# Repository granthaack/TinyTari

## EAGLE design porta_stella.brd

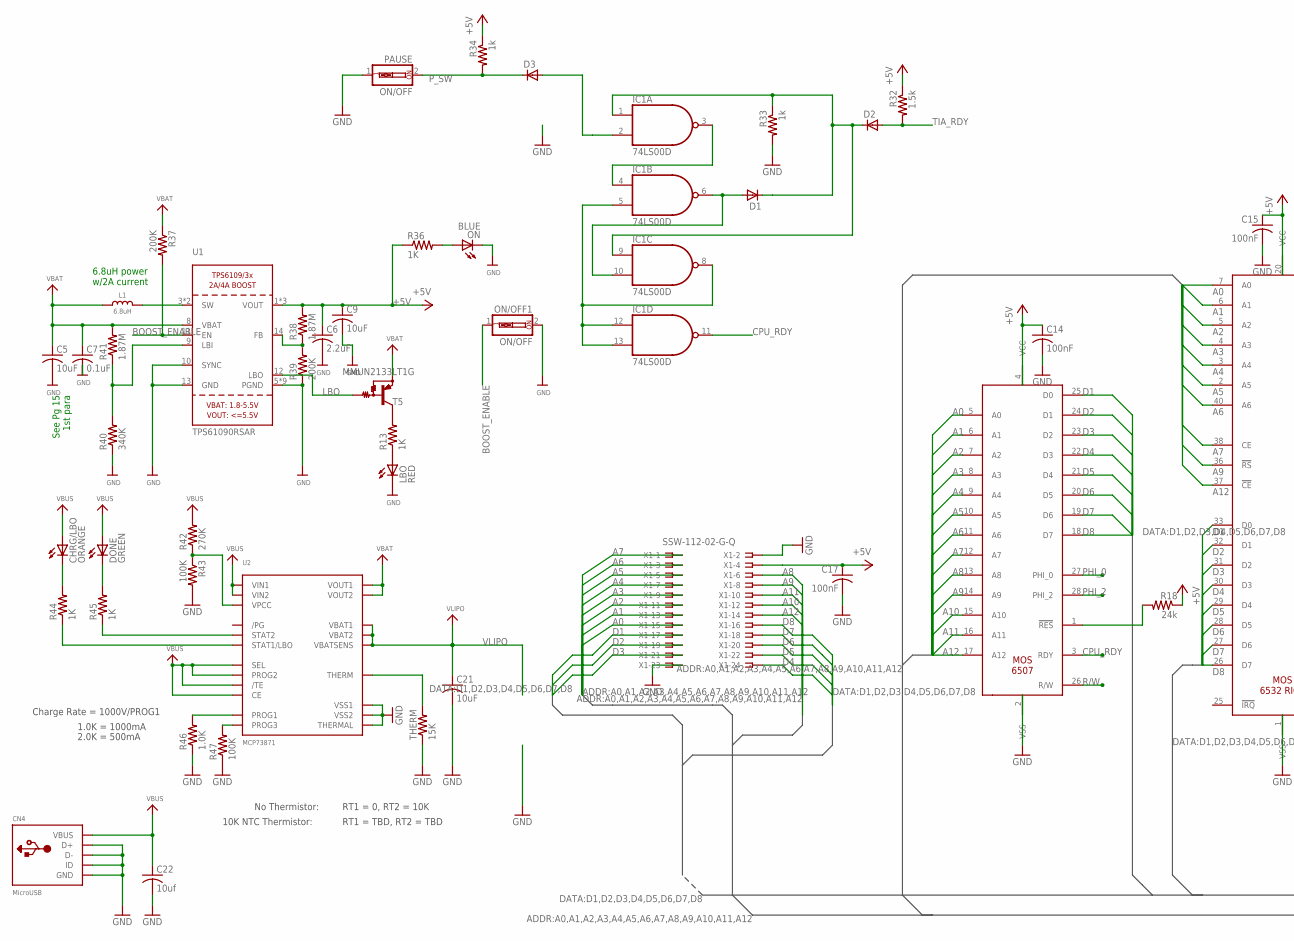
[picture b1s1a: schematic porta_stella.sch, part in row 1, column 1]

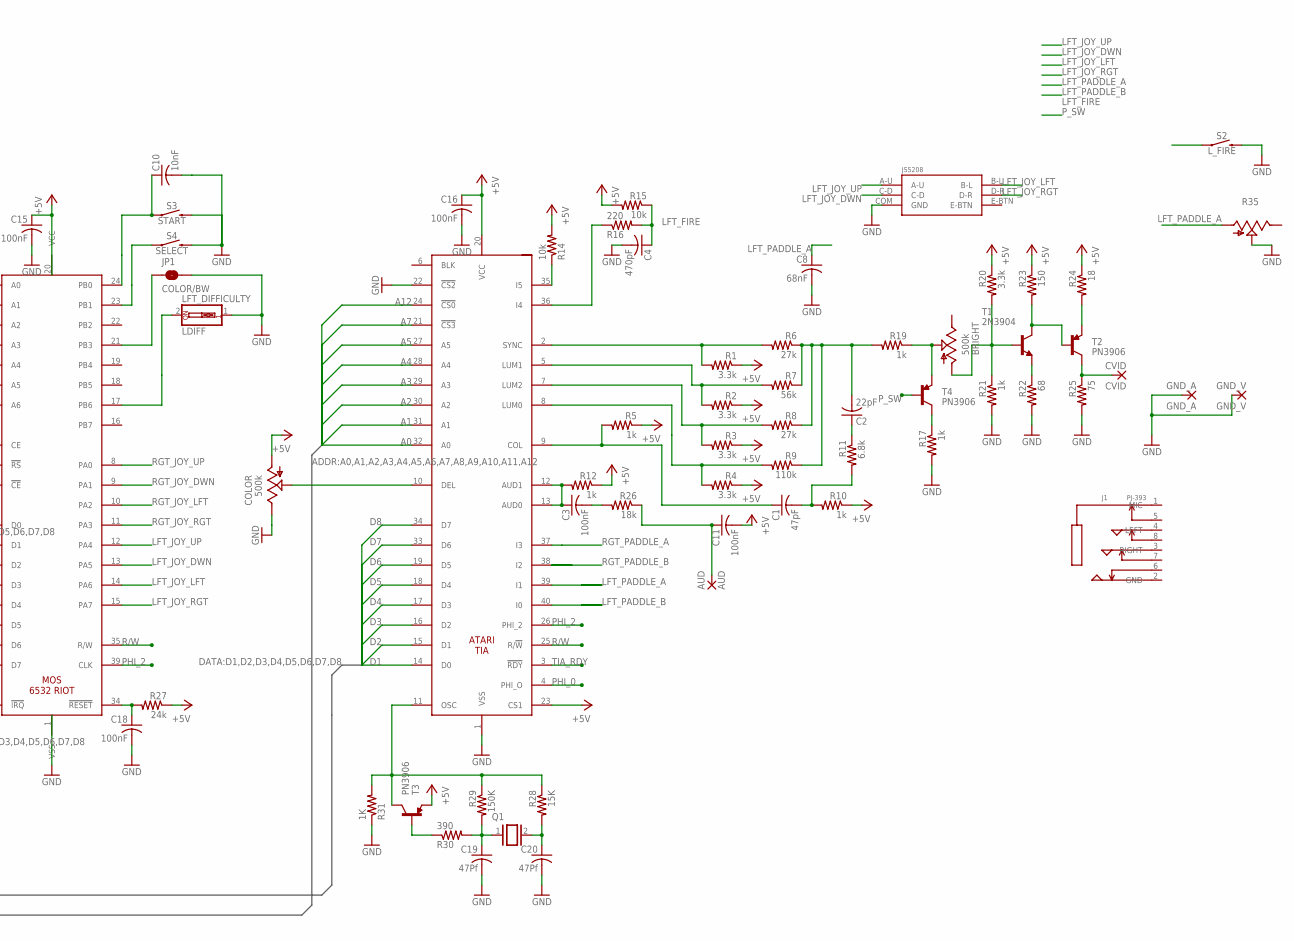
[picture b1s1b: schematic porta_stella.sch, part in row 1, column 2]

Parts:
6507: MOS_6507; DIL28
6532: MOS_6532; DIL40
AUD: AUD; 2,54/1,1
BRIGHT: 500k; 3223G
C1: 47pF; C0805
C2: 22pF; C0805
C3, C11, C14, C15, C16, C17, C18: 100nF; C0805
C4: 470pF; C0805
C5, C9, C21: 10uF; C1210
C6: 2.2uF; C0805
C7: 0.1uF; C0805
C8: 68nF; C0805
C10: 10nF; C0805
C19, C20: 47Pf; C0805
C22: 10uf; C0805
CHRG/LBO: ORANGE; ADAFRUIT_CHIPLED_0603
CN4: MicroUSB; 4UCONN_20329
COLOR: 500k; 3223G
CVID: CVID; 2,54/1,1
D1, D2, D3: DIODE_E-; DIODE_SMB
DONE: GREEN; ADAFRUIT_CHIPLED_0603
GND_A: GND_A; 2,54/1,1
GND_V: GND_V; 2,54/1,1
IC1: 74LS00D; SO14
J1: PJ-393; AUDIO8P-SMD-3.5-14.5X6.1X4.0MM
JP1: COLOR/BW; SMT-JUMPER_2_NO_NO-SILK
L1: 6.8uH; INDUCTOR_5X5MM_TDK_VLC5045
LBO: RED; ADAFRUIT_CHIPLED_0603
LDIFF: LFT_DIFFICULTY; EDG-01
ON: BLUE; ADAFRUIT_CHIPLED_0603
ON/OFF1: ON/OFF; EDG-01
PAUSE: ON/OFF; EDG-01
Q1: XTAL/S; QS
R1, R2, R3, R4, R20: 3.3k; M0805
R5, R10, R12, R17, R19, R21, R33, R34: 1k; M0805
R6, R8: 27k; M0805
R7: 56k; M0805
R9: 110k; M0805
R11: 6.8k; M0805
R13, R36, R44, R45: 1K; R0805
R14, R15: 10k; M0805
R16: 220; M0805
R18, R27: 24k; M0805
R22: 68; M0805
R23: 150; M0805
R24: 18; M0805
R25: 75; M0805
R26: 18k; M0805
R28: 15K; M0805
R29: 150K; M0805
R30: 390; M0805
R31: 1K; M0805
R32: 1.5k; M0805
R35: TRIM_US-ECP10S; ECP10S
R37, R39: 200K; R0805
R38, R41: 1.87M; R0805
R40: 340K; R0805
R42: 270K; R0805
R43, R47: 100K; R0805
R46: 1.0K; R0805
S2: L_FIRE; TACTILE_SWITCH_SMD_5.2MM
S3: START; TACTILE_SWITCH_SMD_6.0X3.5MM
S4: SELECT; TACTILE_SWITCH_SMD_6.0X3.5MM
T1: 2N3904; SOT23-BEC
T2, T3, T4: PN3906; SOT23-3
T5: MMUN2133LT1G; TRANSISTOR_SC59-BEC
THERM: 15K; R0805
TIA: ATARI_TIA; DIL40
U1: TPS61090RSAR; PVQFN-16
U2: MCP73871; QFN20_4MM
U$5: JS5208; JS5208_PKG
X1: SSW-112-02-G-Q

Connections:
+5V: 6507.4 (VCC), 6532.20 (VCC), C6.1, C9.1, C11.2, C14.1, C15.1, C16.1, C17.1, COLOR.1 (A), R1.1, R2.1, R3.1, R4.1, R5.1, R10.1, R12.1, R14.2, R15.2, R18.1, R20.1, R23.1, R24.1, R27.1, R32.1, R34.1, R36.1, R38.2, T3.2 (E), TIA.20 (VCC), TIA.23 (CS1), U1.1 (VOUT), U1.15 (VOUT), U1.16 (VOUT), X1.4
A0: 6507.5 (A0), 6532.7 (A0), TIA.32 (A0), X1.15
A1: 6507.6 (A1), 6532.6 (A1), TIA.31 (A1), X1.13
A2: 6507.7 (A2), 6532.5 (A2), TIA.30 (A2), X1.11
A3: 6507.8 (A3), 6532.4 (A3), TIA.29 (A3), X1.9
A4: 6507.9 (A4), 6532.3 (A4), TIA.28 (A4), X1.7
A5: 6507.10 (A5), 6532.2 (A5), TIA.27 (A5), X1.5
A6: 6507.11 (A6), 6532.40 (A6), X1.3
A7: 6507.12 (A7), 6532.38 (CE), TIA.21 (!CS3), X1.1
A8: 6507.13 (A8), X1.6
A9: 6507.14 (A9), 6532.36 (!RS), X1.8
A10: 6507.15 (A10), X1.12
A11: 6507.16 (A11), X1.10
A12: 6507.17 (A12), 6532.37 (!CE), TIA.24 (!CS0), X1.14
BOOST_ENABLE: ON/OFF1.1, R37.2, U1.11 (EN); also elsewhere on the board
CPU_RDY: 6507.3 (RDY), IC1.11 (O)
CVID: CVID.1, R25.1, T2.3 (C); also elsewhere on the board
D1: 6507.25 (D0), 6532.33 (D0), TIA.14 (D0), X1.17
D2: 6507.24 (D1), 6532.32 (D1), TIA.15 (D1), X1.19
D3: 6507.23 (D2), 6532.31 (D2), TIA.16 (D2), X1.21
D4: 6507.22 (D3), 6532.30 (D3), TIA.17 (D3), X1.24
D5: 6507.21 (D4), 6532.29 (D4), TIA.18 (D4), X1.22
D6: 6507.20 (D5), 6532.28 (D5), TIA.19 (D5), X1.20
D7: 6507.19 (D6), 6532.27 (D6), TIA.33 (D6), X1.18
D8: 6507.18 (D7), 6532.26 (D7), TIA.34 (D7), X1.16
GND: 6507.2 (VSS), 6532.1 (VSS), C4.2, C5.2, C6.2, C7.2, C8.2, C9.2, C10.2, C14.2, C15.2, C16.2, C17.2, C18.2, C19.2, C20.2, C21.2, C22.2, CN4.BASE@1 (GND), CN4.BASE@2 (GND), CN4.D+, CN4.D-, CN4.GND, CN4.ID, CN4.SPRT@1 (GND), CN4.SPRT@2 (GND), CN4.SPRT@3 (GND), CN4.SPRT@4 (GND), COLOR.3 (E), GND_A.1, GND_V.1, IC1.7 (GND), J1.-, JP1.2, LBO.C, LDIFF.1, ON.C, ON/OFF1.2, PAUSE.1, PAUSE.P$1, PAUSE.P$2, PAUSE.P$4, PAUSE.P$5, R17.2, R21.2, R22.2, R25.2, R31.1, R33.2, R35.S, R39.1, R40.1, R43.2, R46.1, R47.1, S2.3 (2), S3.2, S4.2, THERM.1, TIA.1 (VSS), TIA.22 (!CS2), U1.5 (PGND), U1.6 (PGND), U1.7 (PGND), U1.10 (SYNC), U1.13 (GND), U1.P$18 (PGND), U1.P$19 (PGND), U1.P$20 (PGND), U1.P$21 (PGND), U1.P$22 (PGND), U1.THERMAL (PGND), U2.P$10 (VSS1), U2.P$11 (VSS2), U2.P$21 (THERMAL), U$5.COM (GND), X1.2, X1.23; also elsewhere on the board
LBO: T5.B, U1.12 (LBO)
LFT_FIRE: C4.1, R15.1, R16.2, S2.1; also elsewhere on the board
LFT_JOY_DWN: 6532.13 (PA5), U$5.C-D; also elsewhere on the board
LFT_JOY_LFT: 6532.14 (PA6), U$5.B-L; also elsewhere on the board
LFT_JOY_RGT: 6532.15 (PA7), U$5.D-R; also elsewhere on the board
LFT_JOY_UP: 6532.12 (PA4), U$5.A-U; also elsewhere on the board
LFT_PADDLE_A: C8.1, R35.A, TIA.39 (I1); also elsewhere on the board
LFT_PADDLE_B: TIA.40 (I0)
unnamed: R1.2, R6.2, TIA.2 (SYNC)
unnamed: R2.2, R7.2, TIA.5 (LUM1)
unnamed: R3.2, R8.2, TIA.7 (LUM2)
unnamed: R4.2, R9.2, TIA.8 (LUM0)
unnamed: C1.1, R5.2, TIA.9 (COL)
unnamed: C1.2, R10.2, R11.2
unnamed: C2.1, R11.1
unnamed: R14.1, TIA.35 (I5)
unnamed: L1.P$2 (2), U1.3 (SW), U1.4 (SW)
unnamed: R16.1, TIA.36 (I4)
unnamed: R40.2, R41.1, U1.9 (LBI)
unnamed 46: BRIGHT.2 (S), R19.1, T4.2 (E); also elsewhere on the board
unnamed 47: BRIGHT.1 (A), R20.2, R21.1, T1.B; also elsewhere on the board
unnamed: R22.1, T1.E
unnamed: R23.2, T1.C, T2.1 (B)
unnamed: COLOR.2 (S), TIA.10 (DEL)
unnamed: 6532.24 (PB0), C10.1, S3.1
unnamed: 6532.23 (PB1), S4.1
unnamed: 6532.21 (PB3), JP1.1
unnamed 54: 6532.17 (PB6), LDIFF.2; also elsewhere on the board
unnamed: LBO.A, R13.1
unnamed: 6507.1 (!RES), R18.2
unnamed: R24.2, T2.2 (E)
unnamed: C3.2, R26.2
unnamed: C3.1, R12.2, TIA.12 (AUD1), TIA.13 (AUD0)
unnamed: 6532.34 (!RESET), C18.1, R27.2
unnamed: C20.1, Q1.2, R28.2
unnamed: C19.1, Q1.1, R29.2, R30.2
unnamed: R28.1, R29.1, R31.2, T3.3 (C), TIA.11 (OSC)
unnamed: R30.1, T3.1 (B)
unnamed: R17.1, T4.3 (C)
unnamed: IC1.5 (I1), IC1.8 (O), IC1.12 (I0), IC1.13 (I1)
unnamed: D3.A (C), IC1.2 (I1)
unnamed: R38.1, R39.2, U1.14 (FB)
unnamed: IC1.3 (O), IC1.4 (I0)
unnamed: D1.A (C), IC1.6 (O), IC1.10 (I1)
unnamed: D1.C (A), D2.C (A), IC1.1 (I0), IC1.9 (I0), R33.1
unnamed: R13.2, T5.C
unnamed: ON.A, R36.2
unnamed: R42.1, R43.1, U2.P$2 (VPCC)
unnamed: R45.1, U2.P$7 (STAT2)
unnamed: R44.1, U2.P$8 (STAT1/LBO)
unnamed: R46.2, U2.P$13 (PROG1)
unnamed: THERM.2, U2.P$5 (THERM)
unnamed: DONE.C, R45.2
unnamed: CHRG/LBO.C, R44.2
unnamed: R47.2, U2.P$12 (PROG3)
PHI_0: 6507.27 (PHI_0), TIA.4 (PHI_O)
PHI_2: 6507.28 (PHI_2), 6532.39 (CLK), TIA.26 (PHI_2)
P_SW: D3.C (A), PAUSE.2, PAUSE.P$3, PAUSE.P$6, R34.2, T4.1 (B)
R/W: 6507.26 (R/W), 6532.35 (R/W), TIA.25 (R/!W)
RAW_CVID: C2.2, R6.1, R7.1, R8.1, R9.1, R19.2
RGT_JOY_DWN: 6532.9 (PA1)
RGT_JOY_LFT: 6532.10 (PA2)
RGT_JOY_RGT: 6532.11 (PA3)
RGT_JOY_UP: 6532.8 (PA0)
RGT_PADDLE_A: TIA.37 (I3)
RGT_PADDLE_B: TIA.38 (I2)
TIA_RDY: D2.A (C), R32.2, TIA.3 (!RDY)
VBAT: C5.1, C7.1, L1.P$1 (1), R37.1, R41.2, T5.E, U1.8 (VBAT), U2.P$1 (VOUT1), U2.P$20 (VOUT2)
VBUS: C22.1, CHRG/LBO.A, CN4.VBUS, DONE.A, R42.2, U2.P$3 (SEL), U2.P$4 (PROG2), U2.P$9 (/TE), U2.P$17 (CE), U2.P$18 (VIN1), U2.P$19 (VIN2)
VCC: IC1.14 (VCC)
VLIPO: C21.1, J1.+, U2.P$14 (VBAT1), U2.P$15 (VBAT2), U2.P$16 (VBATSENS)

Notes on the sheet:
See Pg 15 1st para
6.8uH power w/2A current
Charge Rate = 1000V/PROG1
1.0K = 1000mA
2.0K = 500mA
No Thermistor:
10K NTC Thermistor:
RT1 = 0, RT2 = 10K
RT1 = TBD, RT2 = TBD

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
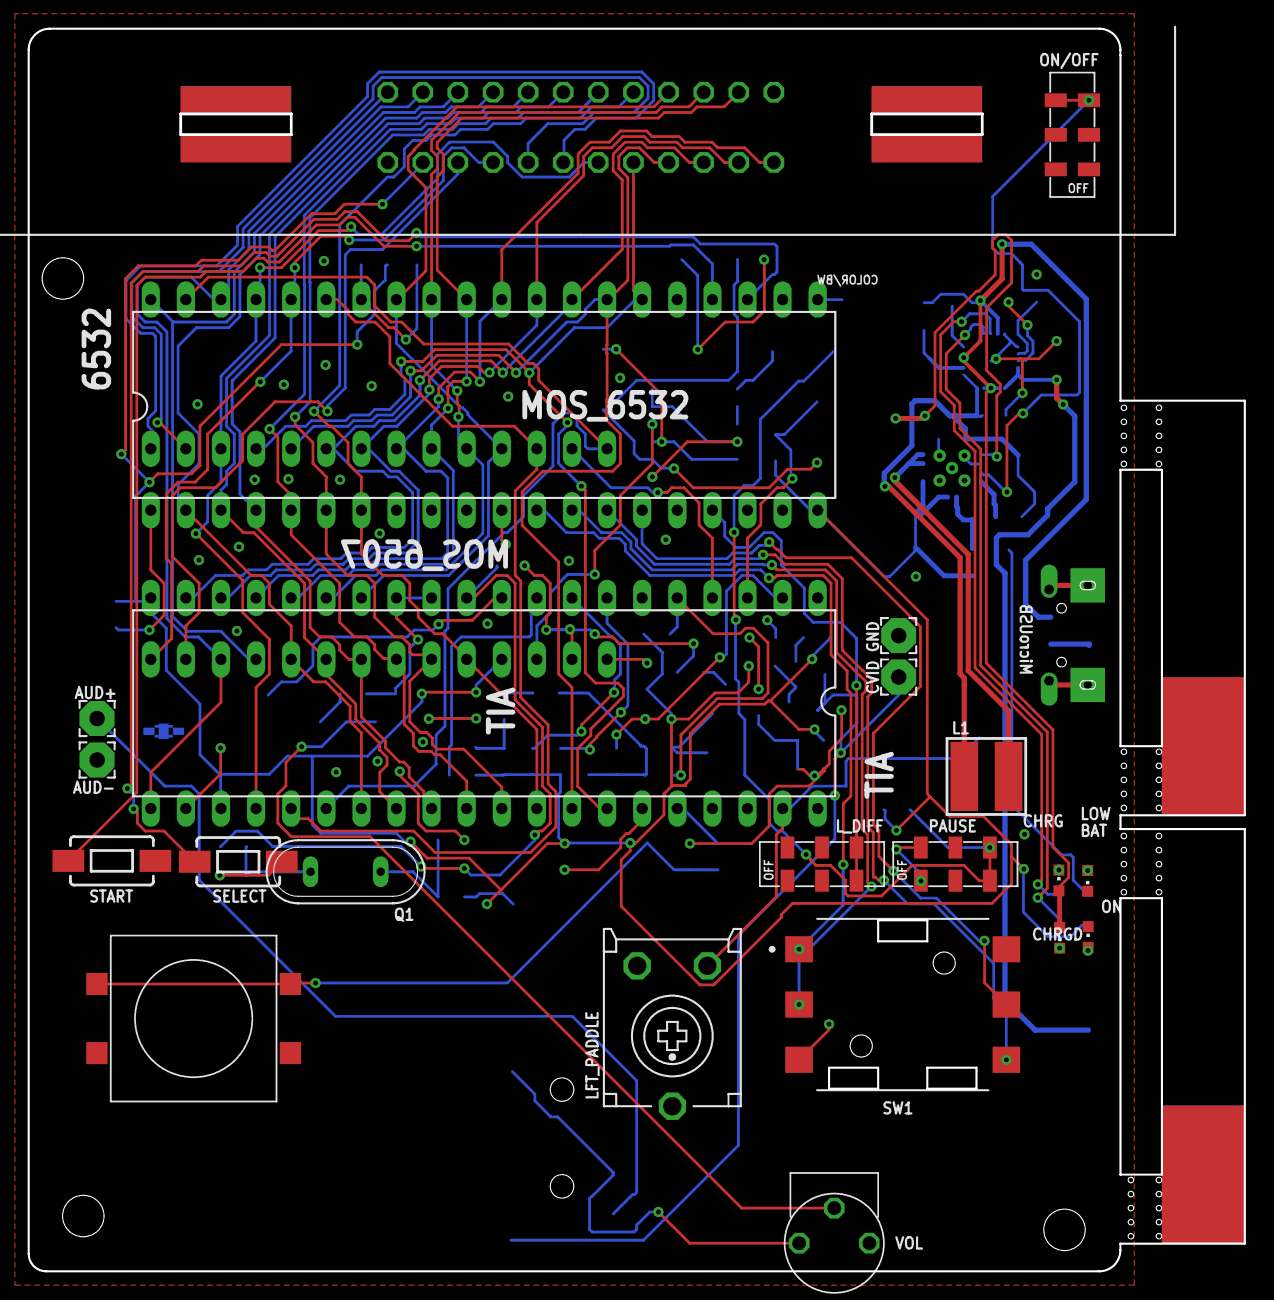
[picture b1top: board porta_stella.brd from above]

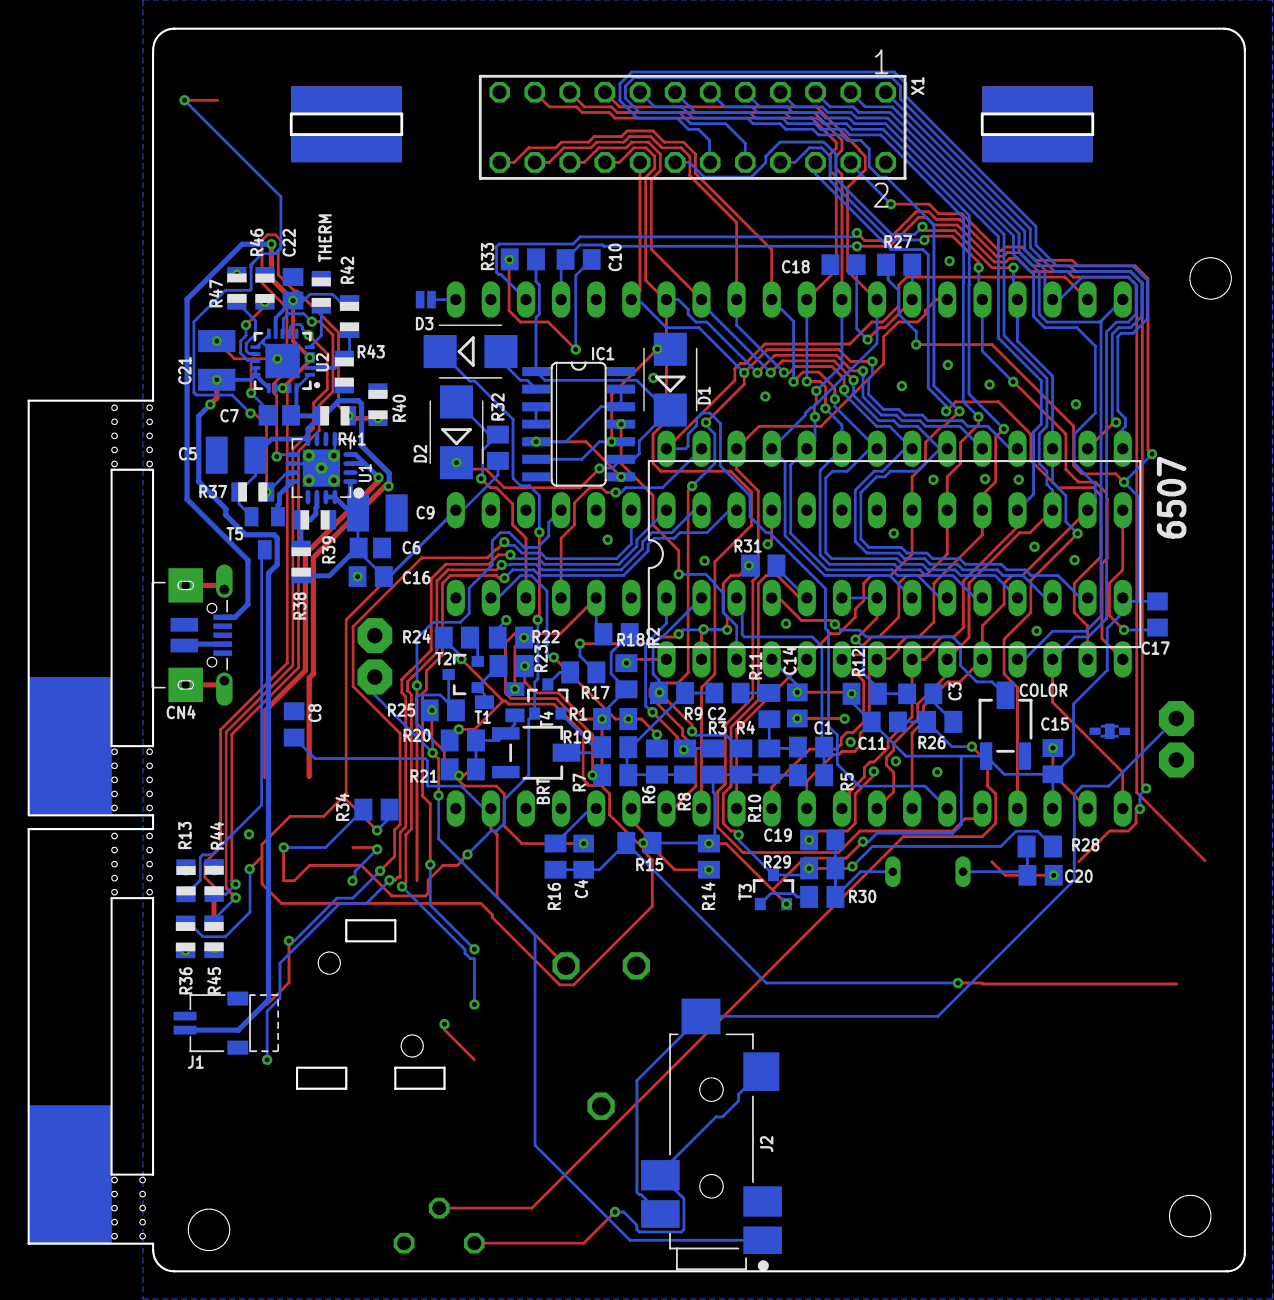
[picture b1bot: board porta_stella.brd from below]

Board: 2 copper layers, 88.0 x 89.9 mm, 108 parts (86 on the bottom side), 92 nets.

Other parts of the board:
BRT: 500k; 3223G
GND_CVID: GND_CVID; 2,54/1,1
GOLD_ORB_SM1: OSHWLOGOLOGO5MM; OSHW_5MM
J2: SJ-43516-SMT; CUI_SJ-43516-SMT
LFT_PADDLE: ECP10S
L_DIFF: JS202011JCQN
ON/OFF: JS202011JCQN
SW1: E-SWITCH_JS5208E-SWITCH_JS5208_0_0; E-SWITCH_JS5208_0
U$7: TL3300DF260Q
VOL: 3352P-1-103LF

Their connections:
AUD: J2.2, J2.3, VOL.P$1
BOOST_ENABLE: ON/OFF.P$3, ON/OFF.P$6; also elsewhere on the board
CVID: J2.1; also elsewhere on the board
GND: GND_CVID.1, J2.4, LFT_PADDLE.S, L_DIFF.P$1, L_DIFF.P$2, L_DIFF.P$4, L_DIFF.P$5, ON/OFF.P$1, ON/OFF.P$2, ON/OFF.P$4, ON/OFF.P$5, SW1.3, U$7.P$3, U$7.P$4, VOL.P$2; also elsewhere on the board
LFT_FIRE: U$7.P$1, U$7.P$2; also elsewhere on the board
LFT_JOY_DWN: SW1.2; also elsewhere on the board
LFT_JOY_LFT: SW1.6; also elsewhere on the board
LFT_JOY_RGT: SW1.5; also elsewhere on the board
LFT_JOY_UP: SW1.1; also elsewhere on the board
LFT_PADDLE_A: LFT_PADDLE.A; also elsewhere on the board
unnamed 46: BRT.2; also elsewhere on the board
unnamed 47: BRT.1; also elsewhere on the board
unnamed 54: L_DIFF.P$3, L_DIFF.P$6; also elsewhere on the board

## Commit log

2018-09-03 labeled everything and started laying traces
2018-09-03 more traces
2018-09-04 added pausing circuitry
2018-09-04 more routing
2018-09-04 even more routing
2018-09-04 added breakout for the power
2018-09-05 swapped the left and right joystick inputs'
    '
2018-09-05 added monogram
2018-09-05 silkscreen work
2018-09-05 yet more silkscreen
2018-09-05 finished silkscreen, probably ready for manufacturing
2018-09-06 started work on portable version
2018-09-07 more layout work for handheld
2018-09-07 more routing work
2018-09-07 Started work on controller daughterboard
2018-09-07 reworked the shape
2018-09-09 more trace work
2018-09-12 included measurements of the screen
2018-09-12 resized again to make more room for the joystick
2018-09-12 switched to gameboy form factor
2018-09-13 Added new switch
2018-09-15 ready to finish wiring
2018-09-23 Finished traces, just need to label components:
2018-09-24 ready for manufacturing
2018-09-25 worked on the BOM
2018-10-07 made gerbers and added a to fix list for rev1.1
2018-10-07 another entry to to-fix
2018-10-07 more stuff to fix
2019-02-10 updated issues

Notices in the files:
parts and their libraries:
SparkFun-Jumpers: Licensing: Creative Commons ShareAlike 4.0 International - https://creativecommons.org/licenses/by-sa/4.0
microbuilder: This work is placed in the public domain, and may be freely used for commercial and non-commercial work with the following conditions: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
